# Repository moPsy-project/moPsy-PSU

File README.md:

# moPsy PSU

> This reposiory contains schematics and PCB files, as well as
> documentation, for the moPsy Power Supply Unit (PSU).

Please make sure you also have the
[moPsy-KiCad-resources](https://github.com/moPsy-project/moPsy-KiCad-resources)
available when opening these projects.

## Status of the Design

I am still in the design process and this is not the final revision.
During the several design stages I have come up with ideas for a simpler
design.
However, at this stage, it would be more expensive to start over than to
build what is available and learn from the iteration. 

More information will appear here as I update the project.

## Contents

This repository is a collection of several projects making up my PSU:

* [BusBoard 1](moPsy_BusBoard_1)
* [BusBoard 2](moPsy_BusBoard_2)
* [Regulator +5V](moPsy_Regulator_5Vpos_BusGate)

PCBs that have been ordered and are in production:

* [Rectifier Board](#11)
* [Regulator 12V positive](#12)
* [Regulator 12V negative](#13)
* [Capacitor Charger](#9)

Parts that are WIP:

* [Capacitor Board](#10)

## License

This work is licensed under a [Creative Commons Attribution-ShareAlike 4.0 International License](http://creativecommons.org/licenses/by-sa/4.0/).

Exception: The moPsy logo is © 2021-2024 Stefan Haun

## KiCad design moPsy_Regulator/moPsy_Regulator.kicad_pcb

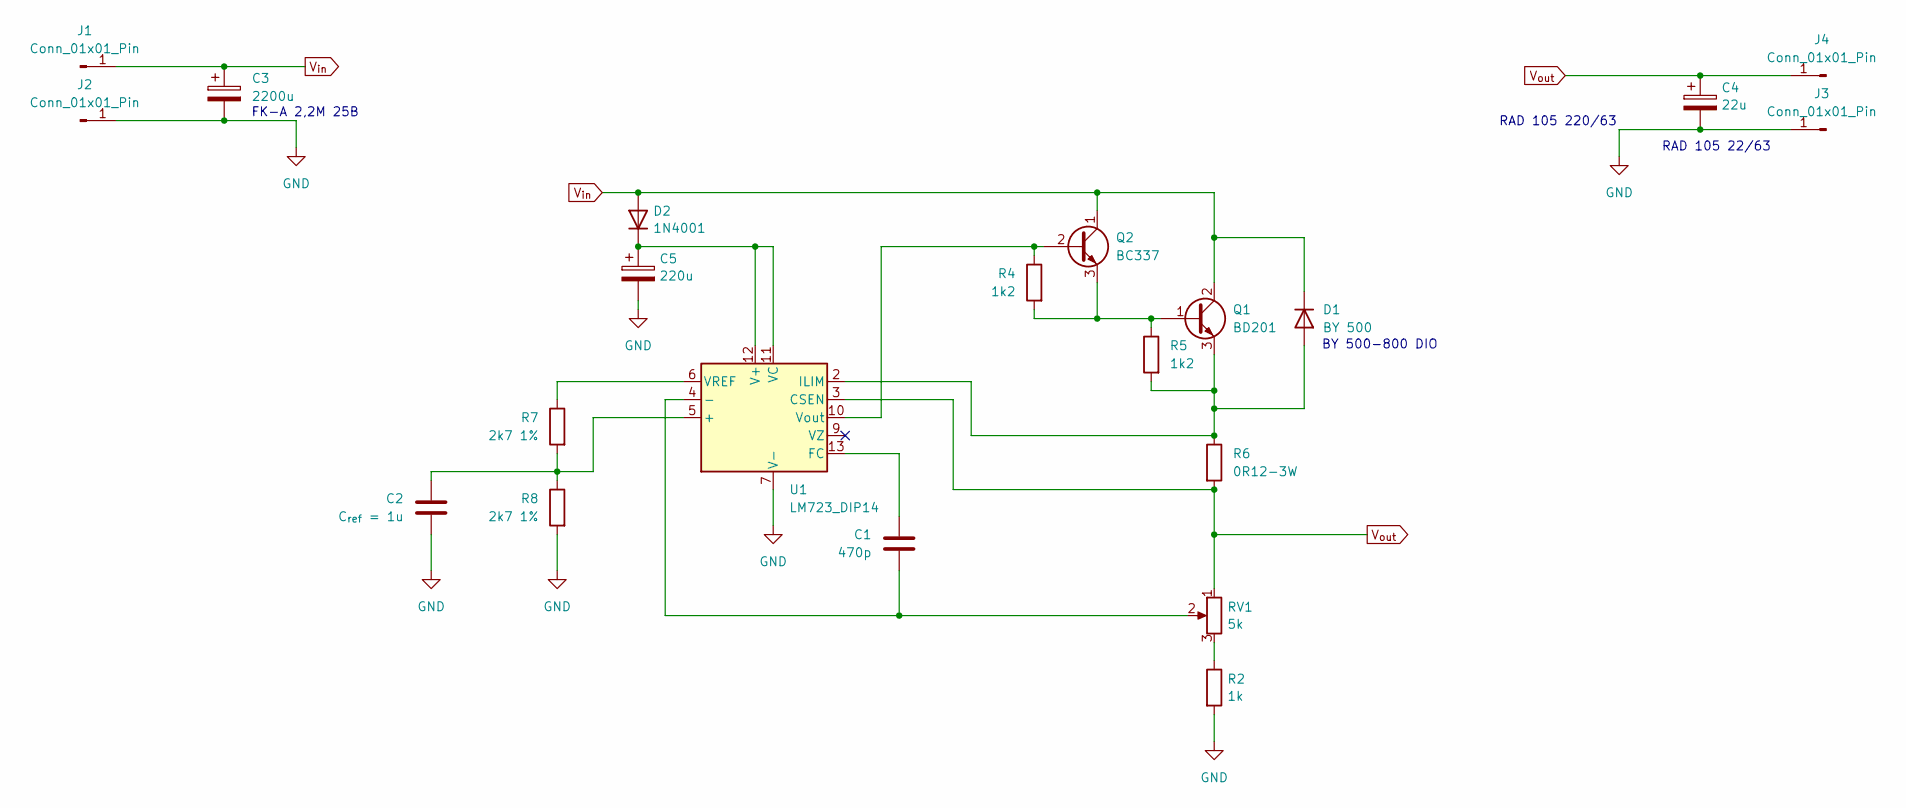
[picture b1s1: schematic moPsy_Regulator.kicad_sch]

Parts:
C1: 470p; C_Disc_D4.3mm_W1.9mm_P5.00mm
C2: C_{ref} = 1u; C_Disc_D4.3mm_W1.9mm_P5.00mm
C3: 2200u; CP_Radial_D16.0mm_P7.50mm
C4: 22u; CP_Radial_D6.3mm_P2.50mm
C5: 220u; CP_Radial_D10.0mm_P5.00mm
D1: BY 500; D_DO-201_P12.70mm_Horizontal
D2: 1N4001; D_DO-41_SOD81_P7.62mm_Horizontal
J1, J2, J3, J4: Conn_01x01_Pin; Connector FS-P475
Q1: BD201; TO-220-3_Vertical
Q2: BC337; TO-92_HandSolder
R2: 1k; R_Axial_DIN0207_L6.3mm_D2.5mm_P7.62mm_Horizontal
R4, R5: 1k2; R_Axial_DIN0207_L6.3mm_D2.5mm_P7.62mm_Horizontal
R6: 0R12-3W; R_Axial_DIN0614_L14.3mm_D5.7mm_P15.24mm_Horizontal
R7, R8: 2k7 1%; R_Axial_DIN0207_L6.3mm_D2.5mm_P7.62mm_Horizontal
RV1: 5k; Potentiometer_Piher_PT-10-V10_Vertical
U1: LM723_DIP14; DIP-14_W7.62mm_LongPads

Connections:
GND: C2.2, C3.2, C4.2, C5.2, J2.1, J3.1, R2.2, R8.2, U1.7 (V-)
unnamed: D1.2 (A), Q1.3 (E), R5.2, R6.1, U1.2 (ILIM)
unnamed: C5.1, D2.1 (K), U1.11 (VC), U1.12 (V+)
unnamed: Q1.1 (B), Q2.3 (E), R4.2, R5.1
unnamed: Q2.2 (B), R4.1, U1.10 (Vout)
unnamed: R2.1, RV1.3
unnamed: C2.1, R7.2, R8.1, U1.5 (+)
unnamed: C1.2, RV1.2, U1.4 (-)
unnamed: C1.1, U1.13 (FC)
unnamed: R7.1, U1.6 (VREF)
V_{in}: C3.1, D1.1 (K), D2.2 (A), J1.1, Q1.2 (C), Q2.1 (C)
V_{out}: C4.1, J4.1, R6.2, RV1.1, U1.3 (CSEN)

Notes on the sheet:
BY 500-800 DIO
RAD 105 22/63
RAD 105 220/63
FK-A 2,2M 25B

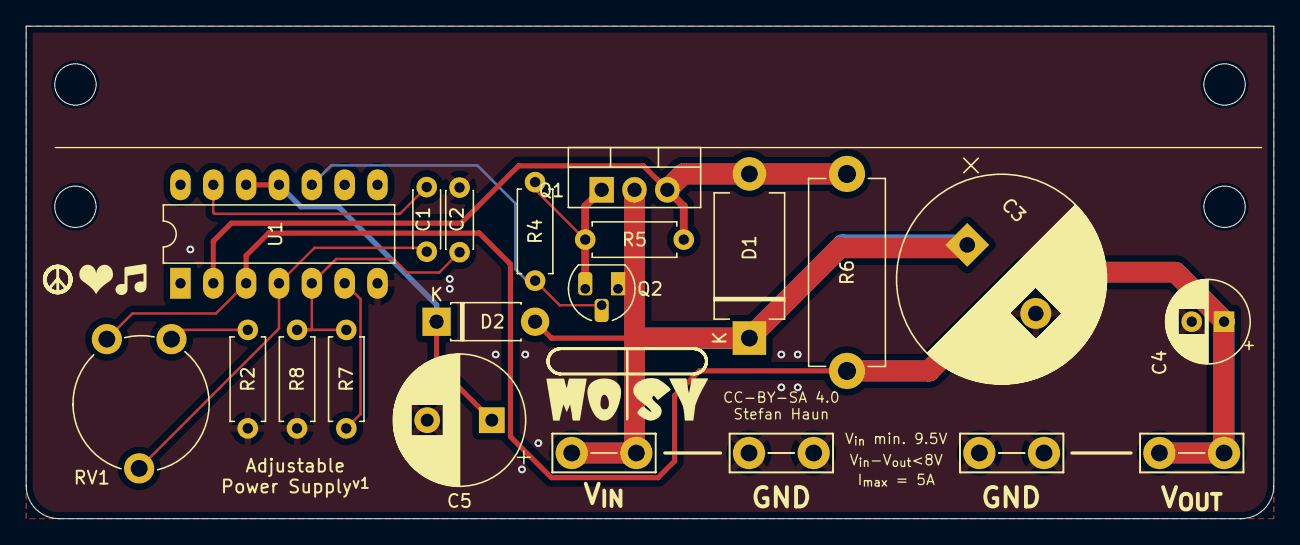
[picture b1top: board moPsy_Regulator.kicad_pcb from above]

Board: 2 copper layers, 96.5 x 38.1 mm, 25 parts (0 on the bottom side), 12 nets.

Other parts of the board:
REF1, REF1#2, REF2, REF2#2: MountingHole_3.2mm_M3

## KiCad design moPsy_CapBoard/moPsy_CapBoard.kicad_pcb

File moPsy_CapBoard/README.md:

# moPsy PSU: Capacitor Board

> Simple board to add another set of reservoir capacitors

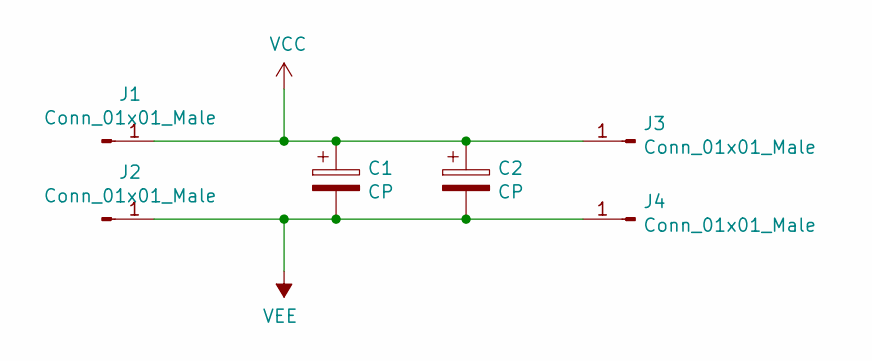
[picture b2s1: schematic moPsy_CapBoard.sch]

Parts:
C1, C2: CP; CP_Radial_D22.0mm_P10.00mm_SnapIn
J1, J2, J3, J4: Conn_01x01_Male; Connector FS-P475

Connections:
VCC: C1.1, C2.1, J1.1, J3.1
VEE: C1.2, C2.2, J2.1, J4.1

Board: 2 copper layers, 7 parts (1 on the bottom side), 2 nets, no tracks yet.

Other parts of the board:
Ref**: Val**; moPsy_logo_kicad_20x09_FSilk

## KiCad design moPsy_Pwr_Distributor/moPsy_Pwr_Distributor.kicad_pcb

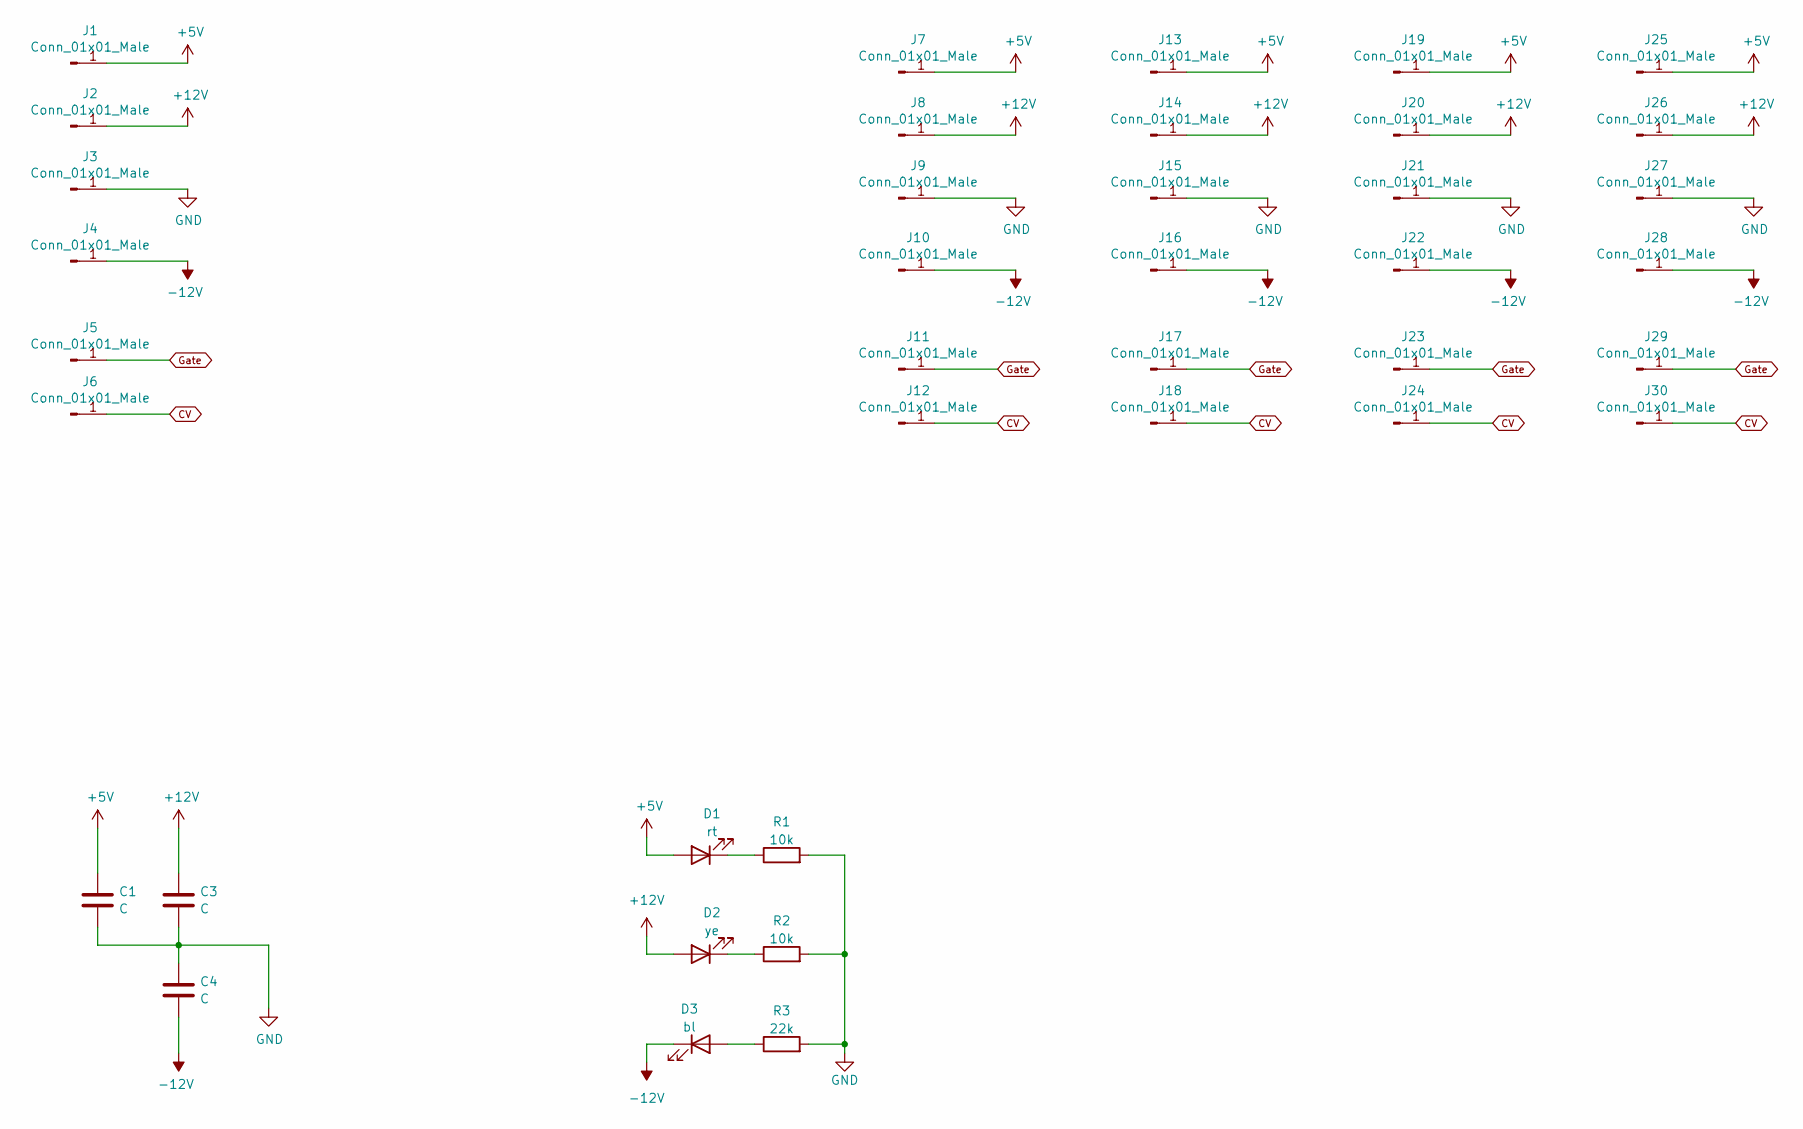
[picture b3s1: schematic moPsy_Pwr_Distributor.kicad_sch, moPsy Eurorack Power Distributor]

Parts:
C1, C3, C4: C; C_Rect_L7.0mm_W2.5mm_P5.00mm
D1: rt; LED_D3.0mm
D2: ye; LED_D3.0mm
D3: bl; LED_D3.0mm
J1, J2, J3, J4, J7, J8, J9, J10, J13, J14, J15, J16, J19, J20, J21, J22, J25, J26, J27, J28: Conn_01x01_Male; Connector FS-P475
J5, J6, J11, J12, J17, J18, J23, J24, J29, J30: Conn_01x01_Male; Pin_D0.9mm_L10.0mm_W2.4mm_FlatFork
R1, R2: 10k; R_Axial_DIN0207_L6.3mm_D2.5mm_P7.62mm_Horizontal
R3: 22k; R_Axial_DIN0207_L6.3mm_D2.5mm_P7.62mm_Horizontal

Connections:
+5V: C1.1, D1.2 (A), J1.1, J7.1, J13.1, J19.1, J25.1
+12V: C3.1, D2.2 (A), J2.1, J8.1, J14.1, J20.1, J26.1
-12V: C4.2, D3.1 (K), J4.1, J10.1, J16.1, J22.1, J28.1
CV: J6.1, J12.1, J18.1, J24.1, J30.1
GND: C1.2, C3.2, C4.1, J3.1, J9.1, J15.1, J21.1, J27.1, R1.2, R2.2, R3.2
Gate: J5.1, J11.1, J17.1, J23.1, J29.1
unnamed: D1.1 (K), R1.1
unnamed: D2.1 (K), R2.1
unnamed: D3.2 (A), R3.1

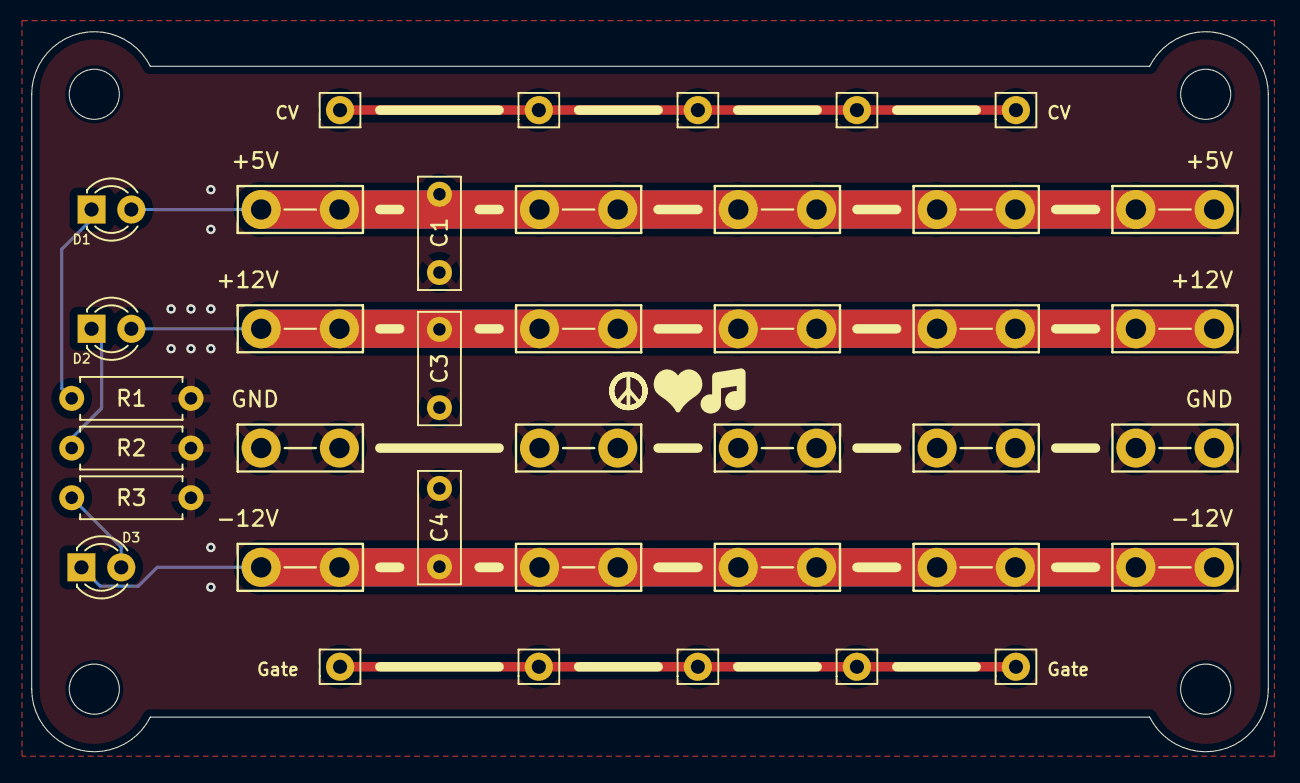
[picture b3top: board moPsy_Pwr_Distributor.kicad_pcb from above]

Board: 2 copper layers, 79.0 x 46.0 mm, 39 parts (0 on the bottom side), 9 nets.

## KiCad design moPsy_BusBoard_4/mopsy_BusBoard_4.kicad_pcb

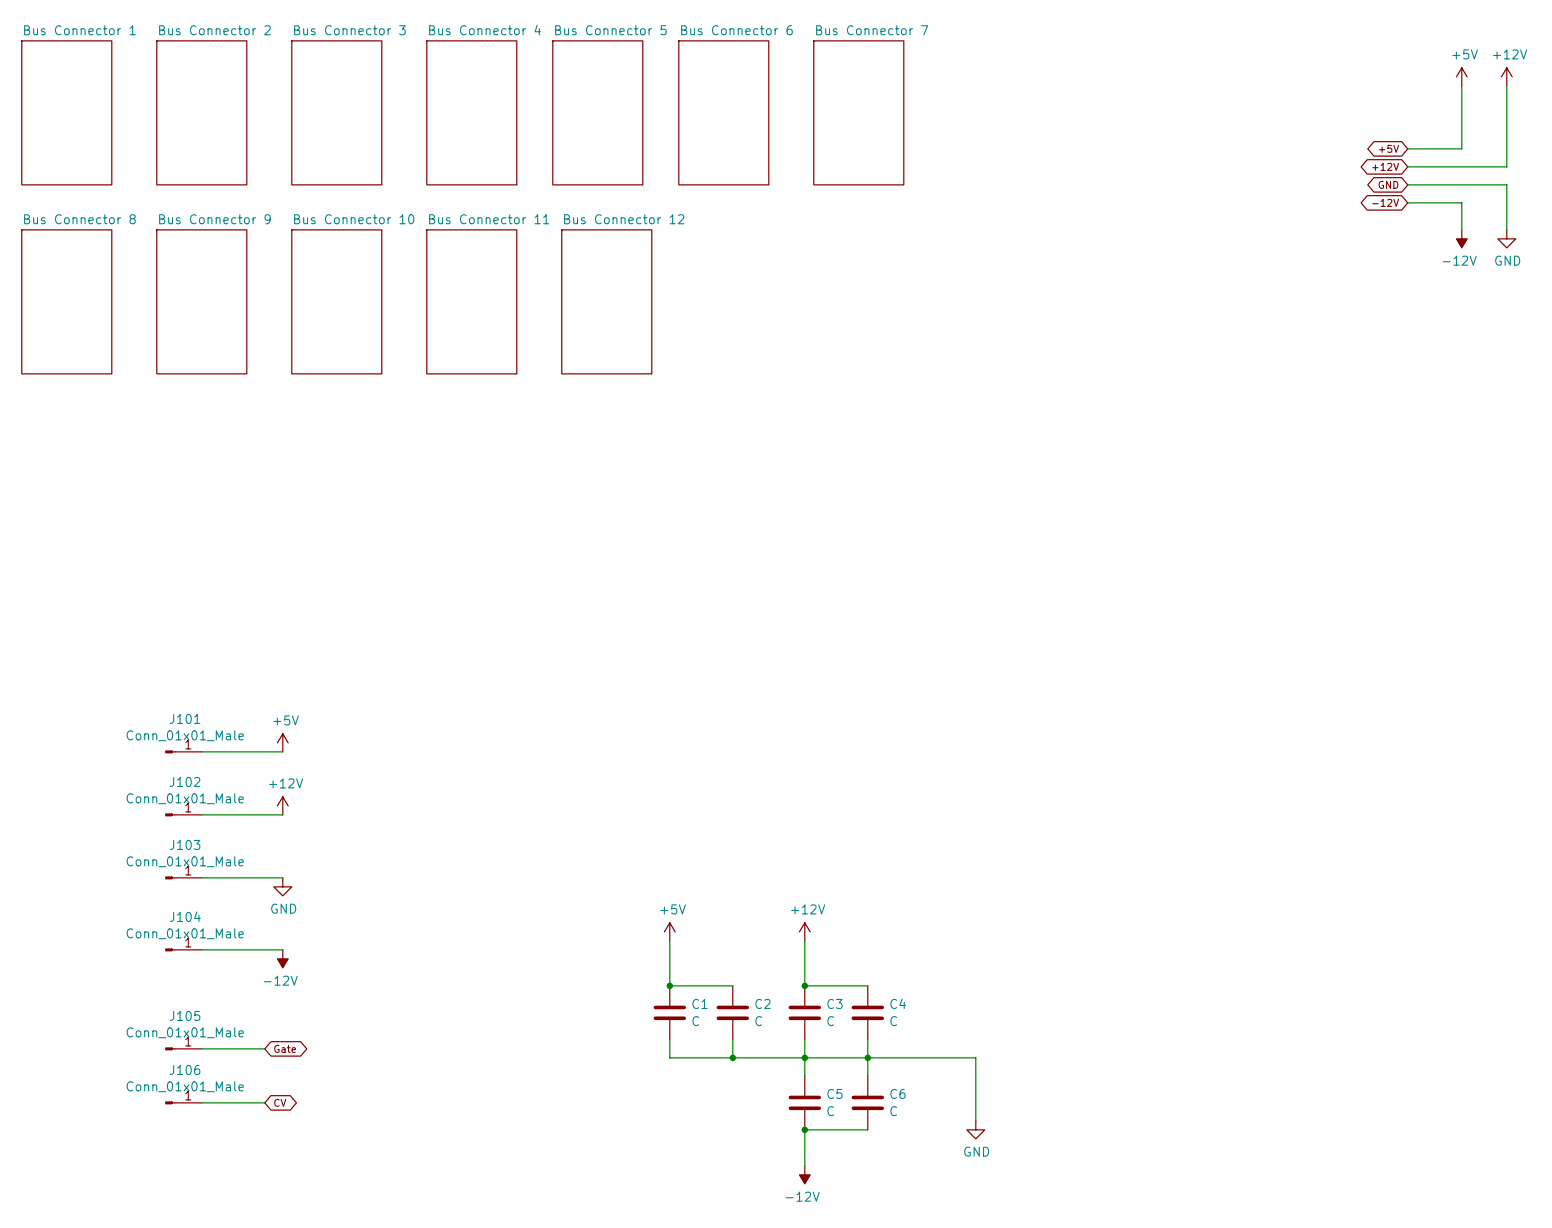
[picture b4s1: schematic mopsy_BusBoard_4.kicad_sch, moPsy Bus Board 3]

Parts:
C1, C2, C3, C4, C5, C6: C; C_Rect_L7.0mm_W2.5mm_P5.00mm
J101, J102, J103, J104: Conn_01x01_Male; Connector FS-P475
J105, J106: Conn_01x01_Male; Pin_D0.9mm_L10.0mm_W2.4mm_FlatFork

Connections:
+5V: C1.1, C2.1, J101.1; also elsewhere on the board
+12V: C3.1, C4.1, J102.1; also elsewhere on the board
-12V: C5.2, C6.2, J104.1; also elsewhere on the board
CV: J106.1; also elsewhere on the board
GND: C1.2, C2.2, C3.2, C4.2, C5.1, C6.1, J103.1; also elsewhere on the board
Gate: J105.1; also elsewhere on the board

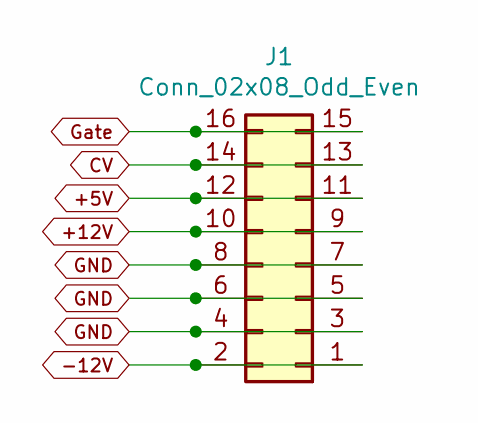
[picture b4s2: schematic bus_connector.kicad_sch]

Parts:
J1: Conn_02x08_Odd_Even; PinHeader_2x08_P2.54mm_Vertical

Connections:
+5V: J1.11, J1.12; also elsewhere on the board
+12V: J1.9, J1.10; also elsewhere on the board
-12V: J1.1, J1.2; also elsewhere on the board
CV: J1.13, J1.14; also elsewhere on the board
GND: J1.3, J1.4, J1.5, J1.6, J1.7, J1.8; also elsewhere on the board
Gate: J1.15, J1.16; also elsewhere on the board

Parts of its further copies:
J2, J3, J4, J5, J6, J7, J8, J9, J10, J11, J12: Conn_02x08_Odd_Even; PinHeader_2x08_P2.54mm_Vertical

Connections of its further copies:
+5V: J2.11, J2.12, J3.11, J3.12, J4.11, J4.12, J5.11, J5.12, J6.11, J6.12, J7.11, J7.12, J8.11, J8.12, J9.11, J9.12, J10.11, J10.12, J11.11, J11.12, J12.11, J12.12; also elsewhere on the board
+12V: J2.9, J2.10, J3.9, J3.10, J4.9, J4.10, J5.9, J5.10, J6.9, J6.10, J7.9, J7.10, J8.9, J8.10, J9.9, J9.10, J10.9, J10.10, J11.9, J11.10, J12.9, J12.10; also elsewhere on the board
-12V: J2.1, J2.2, J3.1, J3.2, J4.1, J4.2, J5.1, J5.2, J6.1, J6.2, J7.1, J7.2, J8.1, J8.2, J9.1, J9.2, J10.1, J10.2, J11.1, J11.2, J12.1, J12.2; also elsewhere on the board
CV: J2.13, J2.14, J3.13, J3.14, J4.13, J4.14, J5.13, J5.14, J6.13, J6.14, J7.13, J7.14, J8.13, J8.14, J9.13, J9.14, J10.13, J10.14, J11.13, J11.14, J12.13, J12.14; also elsewhere on the board
GND: J2.3, J2.4, J2.5, J2.6, J2.7, J2.8, J3.3, J3.4, J3.5, J3.6, J3.7, J3.8, J4.3, J4.4, J4.5, J4.6, J4.7, J4.8, J5.3, J5.4, J5.5, J5.6, J5.7, J5.8, J6.3, J6.4, J6.5, J6.6, J6.7, J6.8, J7.3, J7.4, J7.5, J7.6, J7.7, J7.8, J8.3, J8.4, J8.5, J8.6, J8.7, J8.8, J9.3, J9.4, J9.5, J9.6, J9.7, J9.8, J10.3, J10.4, J10.5, J10.6, J10.7, J10.8, J11.3, J11.4, J11.5, J11.6, J11.7, J11.8, J12.3, J12.4, J12.5, J12.6, J12.7, J12.8; also elsewhere on the board
Gate: J2.15, J2.16, J3.15, J3.16, J4.15, J4.16, J5.15, J5.16, J6.15, J6.16, J7.15, J7.16, J8.15, J8.16, J9.15, J9.16, J10.15, J10.16, J11.15, J11.16, J12.15, J12.16; also elsewhere on the board

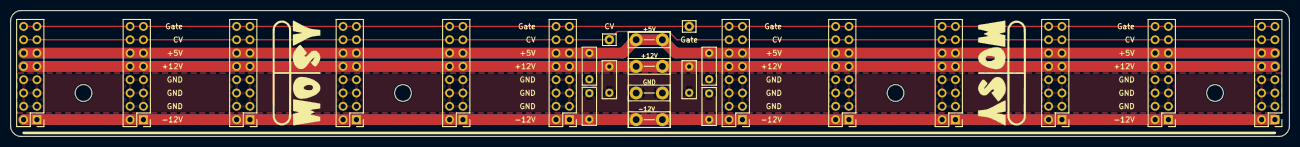
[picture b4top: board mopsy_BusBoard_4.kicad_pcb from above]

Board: 2 copper layers, 244.0 x 24.0 mm, 26 parts (0 on the bottom side), 6 nets.

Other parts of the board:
Ref**: Val**; moPsy_logo_kicad_20x09_FSilk
Ref**#2: Val**; moPsy_logo_kicad_20x09_FSilk

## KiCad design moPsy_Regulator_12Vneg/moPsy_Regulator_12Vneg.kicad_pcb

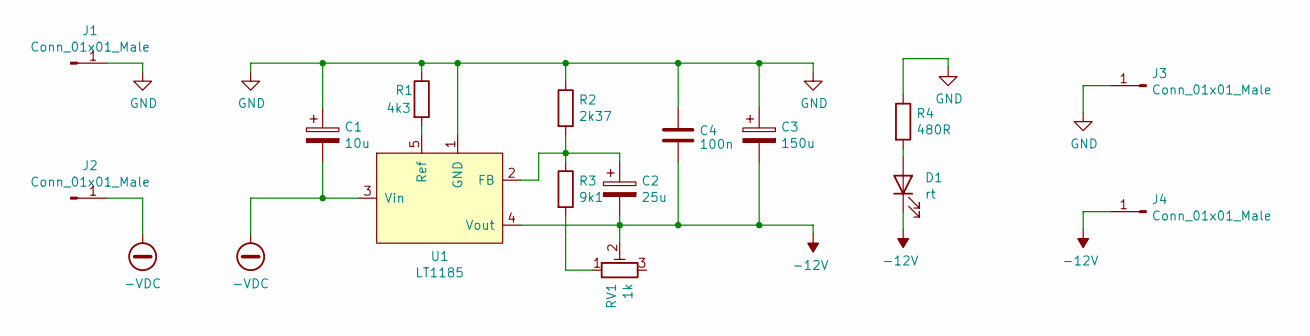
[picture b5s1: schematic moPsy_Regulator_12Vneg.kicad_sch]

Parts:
C1: 10u; CP_Radial_D5.0mm_P2.50mm
C2: 25u; CP_Radial_D5.0mm_P2.00mm
C3: 150u; CP_Radial_D8.0mm_P3.50mm
C4: 100n; C_Rect_L7.0mm_W2.0mm_P5.00mm
D1: rt; LED_D5.0mm
J1, J2, J3, J4: Conn_01x01_Male; Connector FS-P475
R1: 4k3; R_Axial_DIN0207_L6.3mm_D2.5mm_P7.62mm_Horizontal
R2: 2k37; R_Axial_DIN0207_L6.3mm_D2.5mm_P7.62mm_Horizontal
R3: 9k1; R_Axial_DIN0207_L6.3mm_D2.5mm_P7.62mm_Horizontal
R4: 480R; R_Axial_DIN0207_L6.3mm_D2.5mm_P2.54mm_Vertical
RV1: 1k; Suntan 3296 Trim Pot
U1: LT1185; TO-220-5_P3.4x3.7mm_StaggerOdd_Lead3.8mm_Vertical

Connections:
-12V: C2.2, C3.2, C4.2, D1.1 (K), J4.1, RV1.2, U1.4 (Vout)
-VDC: C1.2, J2.1, U1.3 (Vin)
GND: C1.1, C3.1, C4.1, J1.1, J3.1, R1.1, R2.1, R4.1, U1.1 (GND)
unnamed: D1.2 (A), R4.2
unnamed: R3.2, RV1.1
unnamed: C2.1, R2.2, R3.1, U1.2 (FB)
unnamed: R1.2, U1.5 (Ref)

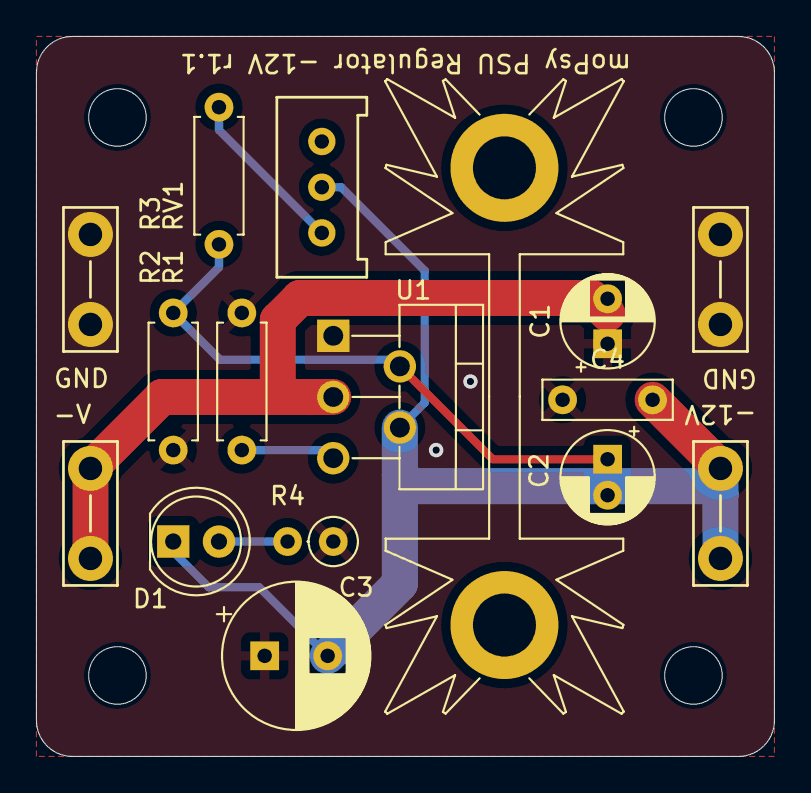
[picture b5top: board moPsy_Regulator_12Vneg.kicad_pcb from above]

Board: 2 copper layers, 41.0 x 40.0 mm, 16 parts (1 on the bottom side), 7 nets.

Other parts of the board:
Ref**: Val**; moPsy_logo_kicad_20x09_FSilk

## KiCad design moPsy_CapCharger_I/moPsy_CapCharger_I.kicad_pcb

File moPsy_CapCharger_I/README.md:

# moPsy PSU: Cap Charger 1

> Charge controller for the load capacitors

The big capacitors want to be charged slowly.

This is a first and very dump version of a charge controller.
Just wait a while until the current limit is lifted and power is
supplied to the Synthesizer.

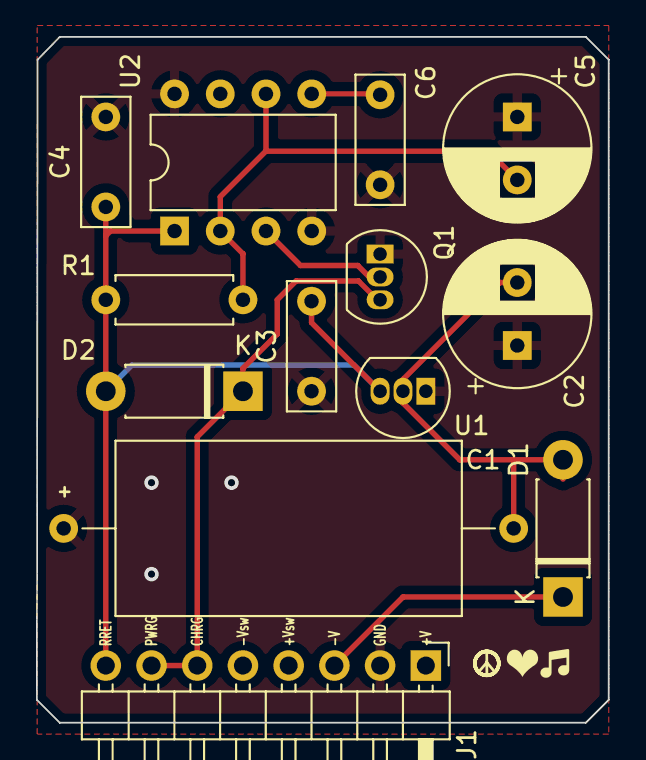
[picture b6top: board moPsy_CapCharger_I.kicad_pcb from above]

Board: 2 copper layers, 31.8 x 38.1 mm, 13 parts (0 on the bottom side), 8 nets.

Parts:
C1: 470u; C_Axial_L19.0mm_D9.5mm_P25.00mm_Horizontal
C2: 33u; CP_Radial_D8.0mm_P3.50mm
C3, C4: 100n; C_Rect_L7.0mm_W2.5mm_P5.00mm
C5: 100u; CP_Radial_D8.0mm_P3.50mm
C6: 10n; C_Rect_L7.0mm_W2.5mm_P5.00mm
D1: 1N4001; D_DO-41_SOD81_P7.62mm_Horizontal
D2: 1N4148; D_DO-41_SOD81_P7.62mm_Horizontal
J1: Conn_01x08_Male; PinHeader_1x08_P2.54mm_Horizontal
Q1: BC547; TO-92_Inline
R1: 47k; R_Axial_DIN0207_L6.3mm_D2.5mm_P7.62mm_Horizontal
U1: LM79L12_TO92; TO-92_Inline
U2: LM555xN; DIP-8_W7.62mm

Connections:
-15V: D1.1 (K), J1.3
GND: C1.1, C2.1, C3.1, C4.1, C5.1, C6.1, J1.2, Q1.1 (C), U1.1 (GND), U2.4 (R), U2.8 (VCC)
unnamed: C1.2, C2.2, D1.2 (A), U1.2 (VI)
unnamed: C5.2, R1.1, U2.2 (TR), U2.6 (THR)
unnamed: C6.2, U2.5 (CV)
unnamed: Q1.2 (B), U2.3 (Q)
REL_Charge: D2.1 (K), J1.6, J1.7, Q1.3 (E)
REL_RETURN: C3.2, C4.2, D2.2 (A), J1.8, R1.2, U1.3 (VO), U2.1 (GND)

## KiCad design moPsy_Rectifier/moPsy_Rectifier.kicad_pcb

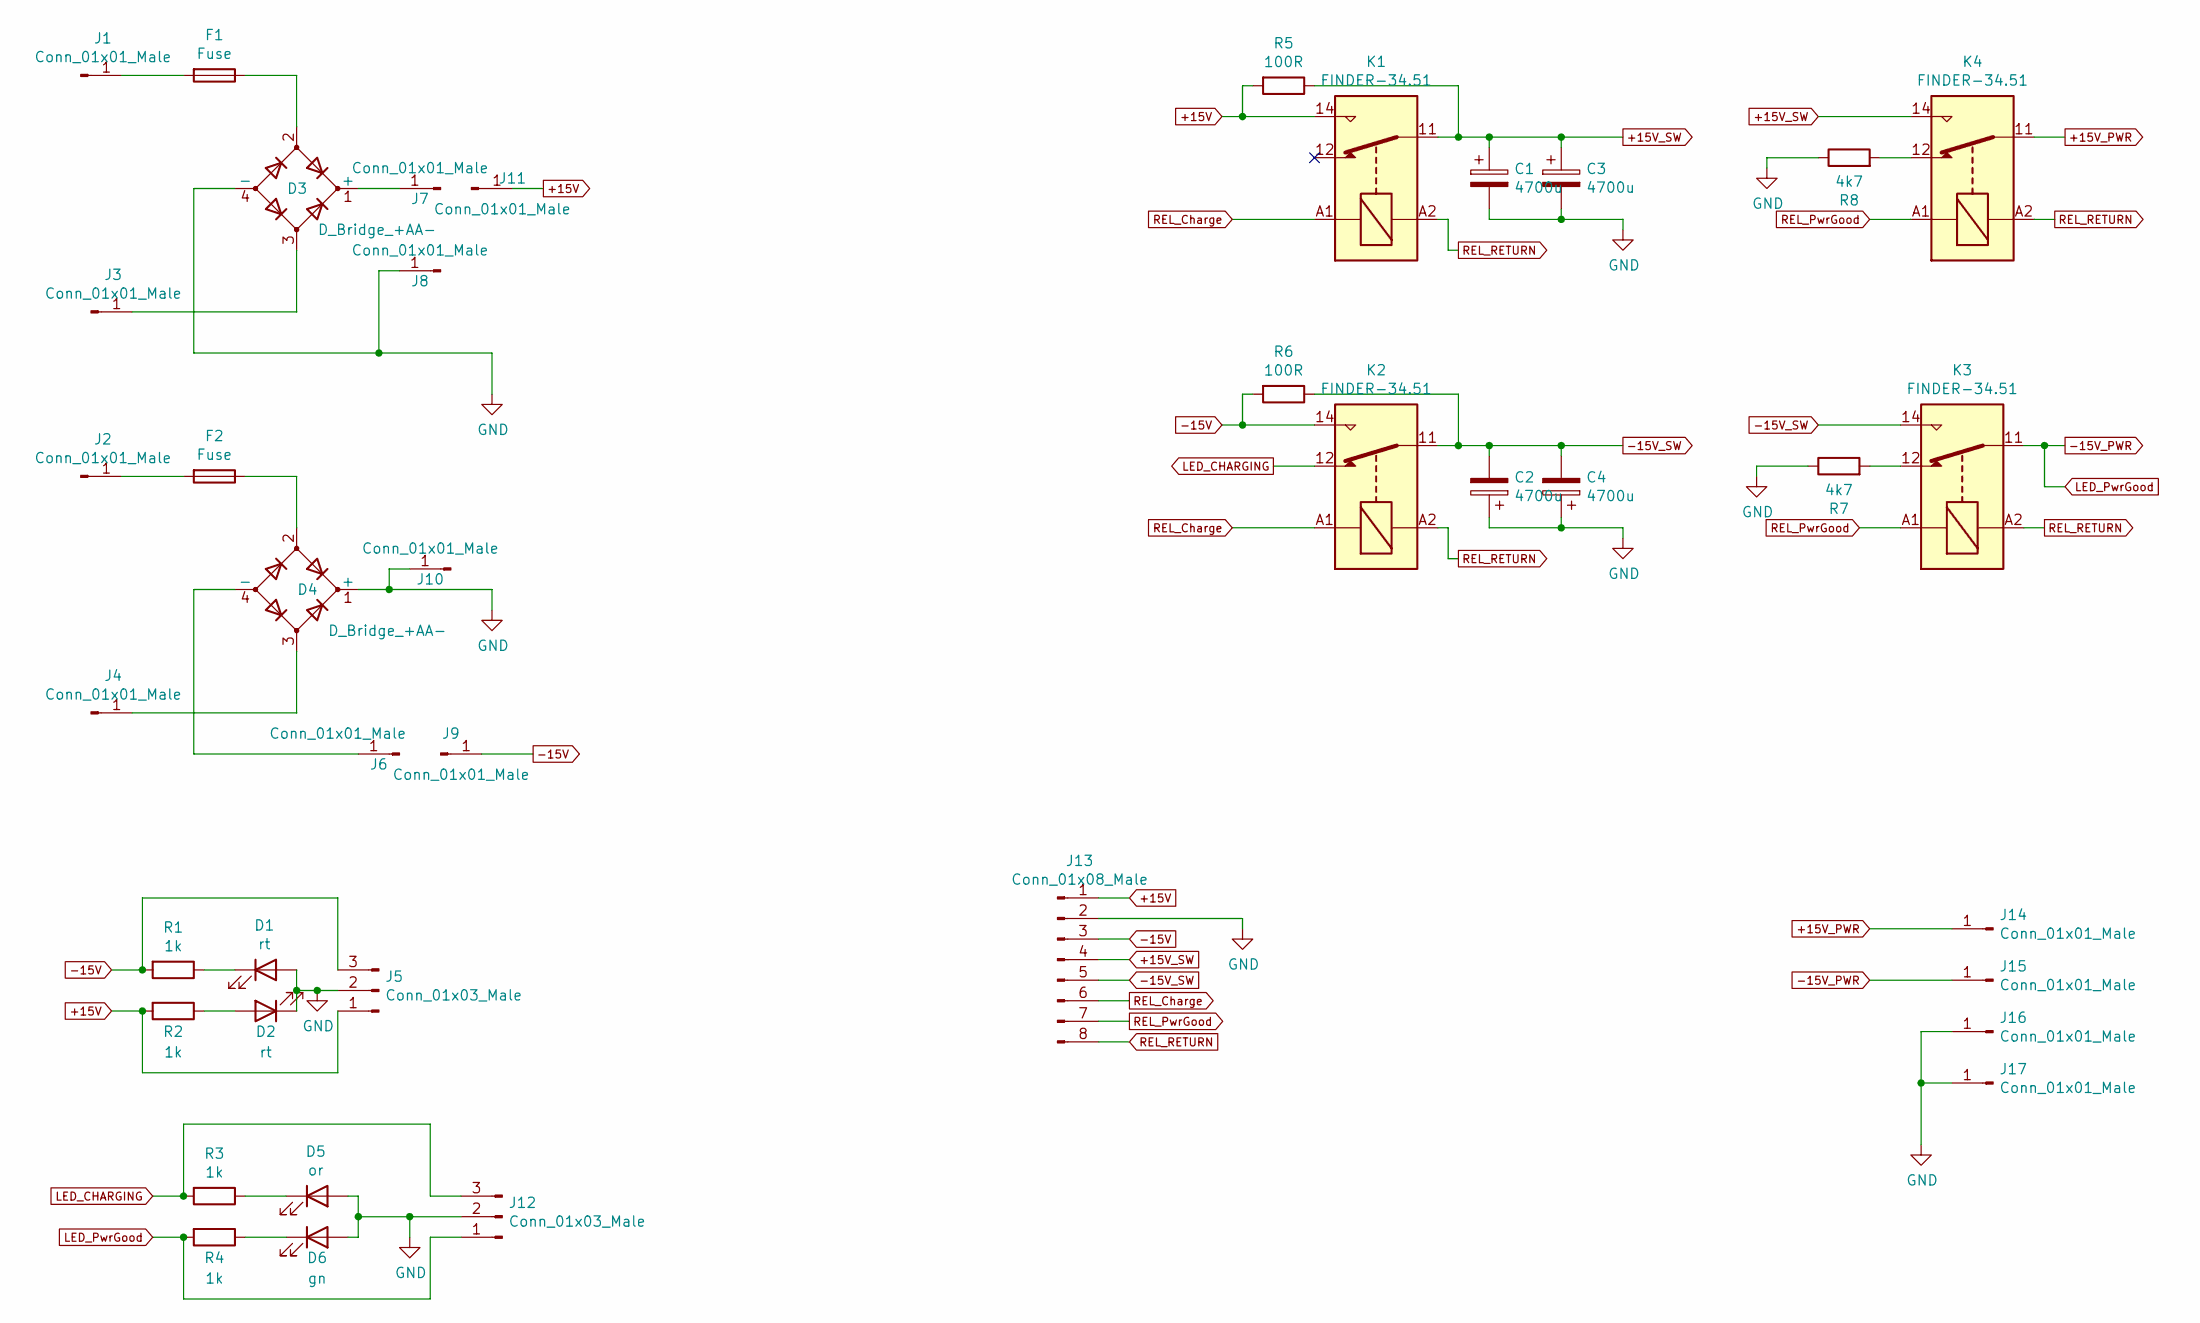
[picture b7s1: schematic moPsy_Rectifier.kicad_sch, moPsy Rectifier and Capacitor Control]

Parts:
C1, C2, C3, C4: 4700u; CP_Radial_D22.0mm_P10.00mm_SnapIn
D1, D2: rt; LED_D5.0mm
D3, D4: D_Bridge_+AA-; Diode_Bridge_32.0x5.6x17.0mm_P10.0mm_P7.5mm
D5: or; LED_D5.0mm
D6: gn; LED_D5.0mm
F1, F2: Fuse; Fuseholder_Cylinder-5x20mm_Stelvio-Kontek_PTF78_Horizontal_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
J1, J2, J3, J4, J6, J7, J8, J9, J10, J11, J14, J15, J16, J17: Conn_01x01_Male; Connector FS-P475
J5, J12: Conn_01x03_Male; PinHeader_1x03_P2.54mm_Vertical
J13: Conn_01x08_Male; PinSocket_1x08_P2.54mm_Vertical
K1, K2, K3, K4: FINDER-34.51; HF41FC
R1, R2, R3, R4: 1k; R_Axial_DIN0309_L9.0mm_D3.2mm_P12.70mm_Horizontal
R5, R6: 100R; R_Axial_DIN0614_L14.3mm_D5.7mm_P5.08mm_Vertical
R7, R8: 4k7; R_Axial_DIN0309_L9.0mm_D3.2mm_P12.70mm_Horizontal

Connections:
+15V: J5.1, J11.1, J13.1, K1.14, R2.2, R5.2
+15V_PWR: J14.1, K4.11
+15V_SW: C1.1, C3.1, J13.4, K1.11, K4.14, R5.1
-15V: J5.3, J9.1, J13.3, K2.14, R1.2, R6.2
-15V_PWR: J12.1, J15.1, K3.11, R4.2
-15V_SW: C2.2, C4.2, J13.5, K2.11, K3.14, R6.1
GND: C1.2, C2.1, C3.2, C4.1, D1.2 (A), D2.1 (K), D3.4 (-), D4.1 (+), D5.2 (A), D6.2 (A), J5.2, J8.1, J10.1, J12.2, J13.2, J16.1, J17.1, R7.1, R8.1
LED_CHARGING: J12.3, K2.12, R3.2
unnamed: D1.1 (K), R1.1
unnamed: D2.2 (A), R2.1
unnamed: D3.1 (+), J7.1
unnamed: D3.2, F1.1
unnamed: D3.3, J3.1
unnamed: D4.2, F2.1
unnamed: D4.3, J4.1
unnamed: D4.4 (-), J6.1
unnamed: D5.1 (K), R3.1
unnamed: D6.1 (K), R4.1
unnamed: F1.2, J1.1
unnamed: F2.2, J2.1
unnamed: K3.12, R7.2
unnamed: K4.12, R8.2
REL_Charge: J13.6, K1.A1, K2.A1
REL_PwrGood: J13.7, K3.A1, K4.A1
REL_RETURN: J13.8, K1.A2, K2.A2, K3.A2, K4.A2

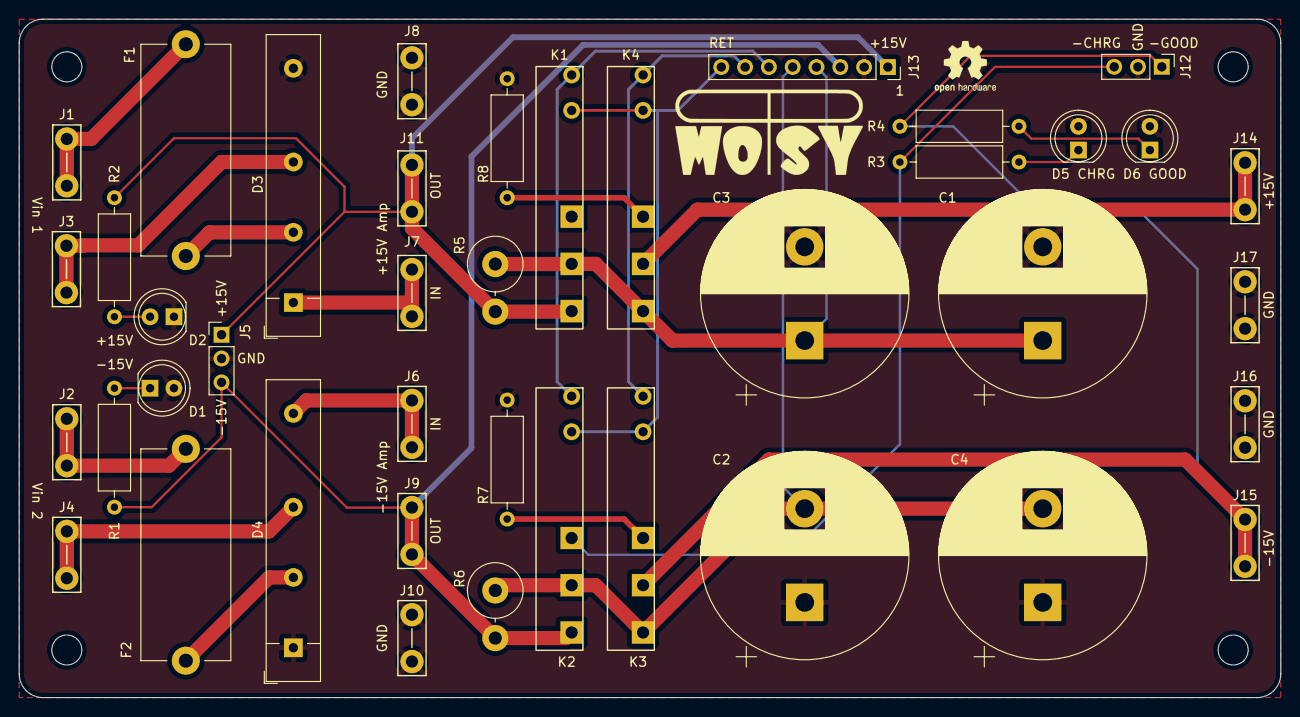
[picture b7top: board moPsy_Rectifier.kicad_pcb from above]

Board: 2 copper layers, 134.6 x 72.4 mm, 42 parts (0 on the bottom side), 25 nets.

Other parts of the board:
Ref**: Val**; moPsy_logo_kicad_20x09_FSilk

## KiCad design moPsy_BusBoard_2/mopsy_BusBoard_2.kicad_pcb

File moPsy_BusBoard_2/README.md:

# moPsy PSU: BusBoard 2

> BusBoard that can be used in two directions

## License

See [License in the main README](../README.md).

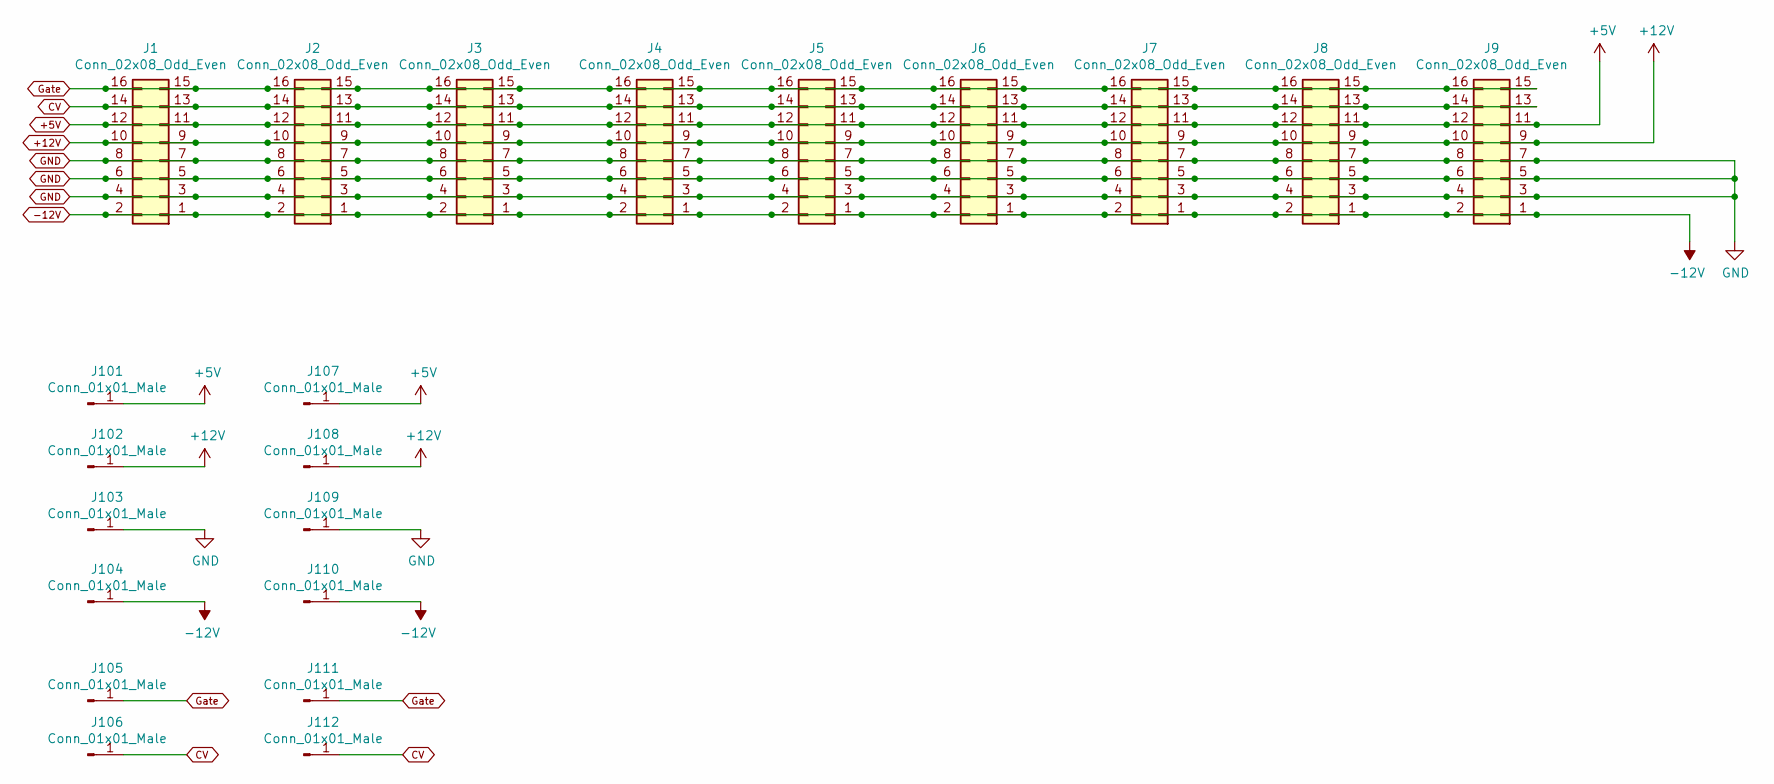
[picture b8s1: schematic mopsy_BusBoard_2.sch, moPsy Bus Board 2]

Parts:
J1, J2, J3, J4, J5, J6, J7, J8, J9: Conn_02x08_Odd_Even; PinHeader_2x08_P2.54mm_Vertical
J101, J102, J103, J104, J107, J108, J109, J110: Conn_01x01_Male; Connector FS-P475
J105, J106, J111, J112: Conn_01x01_Male; Pin_D0.9mm_L10.0mm_W2.4mm_FlatFork

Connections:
+5V: J1.11, J1.12, J2.11, J2.12, J3.11, J3.12, J4.11, J4.12, J5.11, J5.12, J6.11, J6.12, J7.11, J7.12, J8.11, J8.12, J9.11, J9.12, J101.1, J107.1
+12V: J1.9, J1.10, J2.9, J2.10, J3.9, J3.10, J4.9, J4.10, J5.9, J5.10, J6.9, J6.10, J7.9, J7.10, J8.9, J8.10, J9.9, J9.10, J102.1, J108.1
-12V: J1.1, J1.2, J2.1, J2.2, J3.1, J3.2, J4.1, J4.2, J5.1, J5.2, J6.1, J6.2, J7.1, J7.2, J8.1, J8.2, J9.1, J9.2, J104.1, J110.1
CV: J1.13, J1.14, J2.13, J2.14, J3.13, J3.14, J4.13, J4.14, J5.13, J5.14, J6.13, J6.14, J7.13, J7.14, J8.13, J8.14, J9.13, J9.14, J106.1, J112.1
GND: J1.3, J1.4, J1.5, J1.6, J1.7, J1.8, J2.3, J2.4, J2.5, J2.6, J2.7, J2.8, J3.3, J3.4, J3.5, J3.6, J3.7, J3.8, J4.3, J4.4, J4.5, J4.6, J4.7, J4.8, J5.3, J5.4, J5.5, J5.6, J5.7, J5.8, J6.3, J6.4, J6.5, J6.6, J6.7, J6.8, J7.3, J7.4, J7.5, J7.6, J7.7, J7.8, J8.3, J8.4, J8.5, J8.6, J8.7, J8.8, J9.3, J9.4, J9.5, J9.6, J9.7, J9.8, J103.1, J109.1
Gate: J1.15, J1.16, J2.15, J2.16, J3.15, J3.16, J4.15, J4.16, J5.15, J5.16, J6.15, J6.16, J7.15, J7.16, J8.15, J8.16, J9.15, J9.16, J105.1, J111.1

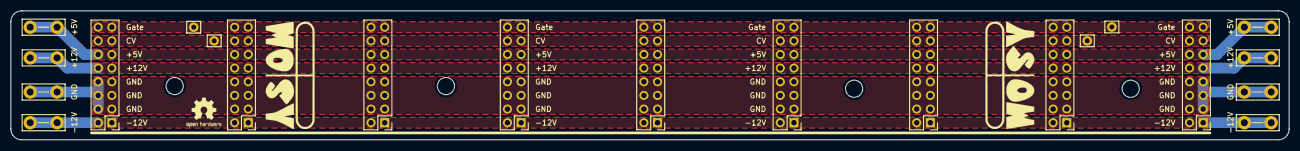
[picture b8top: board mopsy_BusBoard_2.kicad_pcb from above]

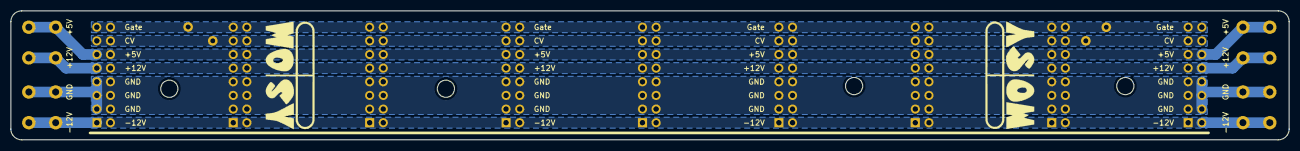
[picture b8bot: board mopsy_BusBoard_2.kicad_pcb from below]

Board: 2 copper layers, 238.0 x 24.0 mm, 25 parts (2 on the bottom side), 6 nets.

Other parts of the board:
Ref**: Val**; moPsy_logo_kicad_20x09_FSilk
Ref**#2, Ref**#3, Ref**#4: Val**; moPsy_logo_kicad_20x09_FSilk

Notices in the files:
moPsy_BusBoard_4/mopsy_BusBoard_4.kicad_pcb:
CC-BY-SA
moPsy_CapCharger_I/moPsy_CapCharger_I.kicad_pcb:
CC BY-SA 4.0
moPsy_Pwr_Distributor/moPsy_Pwr_Distributor.kicad_pcb:
CC-BY-SA Stefan Haun
